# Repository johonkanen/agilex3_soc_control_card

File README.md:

# agilex3_soc_control_card
Agilex 5 SoC based control card for an AC in/out lab power supply.
The original board used an Agilex 3 FPGA and had a few bugs in the pin connections, so this second revision
uses an SoC instead of just an FPGA. The target is a Linux-capable control board with an Ethernet connection.

Main features:
- Agilex 5 E-Series SoC A5EB013B (quad-core HPS), B23B 795-ball package, -6S speed grade
- 1 GB LPDDR4 (SK hynix H9HCNNN8KUMLHR-NMO (fitted from stock; checked against the -NME data sheet), 2 channels x16 = x32), 2133 MT/s on the HPS EMIF
- 16 GB eMMC (KIOXIA THGAMVG7T13BAIL, 8-bit, HPS SD/MMC)
- 128 Mbit QSPI configuration flash (ISSI IS25WP128-RHLE)
- 1 Gb Ethernet (Realtek RTL8211FDI RGMII PHY, HanRun HR911130A MagJack)
- muxed ADC block (ADS7056)

Controls power electronics, so it mostly does generic I/O for PWM and SPI/SDM ADCs.
Built by JLCPCB (8-layer, JLC08161H-3313 stack-up).

The LPDDR4, eMMC and QSPI flash are parts shared with the Agilex 3 card and the Efinix Ti135 board, see
`SHARED_PARTS.md`.

## Status

- **LPDDR4 routing: done and tuned (2026-10-31).** All 54 nets (U7 bank 3 to U12) are routed and delay-matched
  with KiCad's time-domain tuner against the Altera 821801 budgets (`LPDDR4_DELAY_REPORT.md`, generated by
  `tools/lpddr4_delay/delay_report.py`):
  - byte spreads 4.5 / 8.8 / 4.5 / 3.3 ps (target 10 ps), DQ-DQS -4.5 ... +8.8 ps (limit -68 ... +43 ps);
  - DQS and CK P/N within 0.1 ps (limit 1 ps), CA/CKE/CS 415.0-417.7 ps die to ball (CK + 10 ps target);
  - no LPDDR4 DRC items, including the 0.2 / 0.3 mm crosstalk spacing rules.
  - IBIS simulation of the routed copper (`sim/lpddr4_si/results/routed.md`): every eye passes at 1600 MT/s
    (typ/min/max corners) and 2133 MT/s (typ).
  - Quartus (`LPDDR4_SWIZZLE_PLAN.md`): the routed pinout and swizzle fit, and a 2133 MT/s build (the -6S
    maximum) meets timing. 2133 MT/s is the design rate.
- **Board fully routed (2026-11-01).** eMMC, QSPI, Ethernet (RGMII, MDI pairs to the MagJack, PHY power and GND
  pours) and the HPS peripherals are routed, all zones are refilled, and the plane outlines are tidied.
  - DRC: 0 errors, 0 unconnected items, 0 schematic-parity issues. The only warning left is J3's intentional
    footprint mismatch (smaller pads and holes than the library); J3's two board-edge items are excluded.
  - ERC: 0 errors, 0 warnings.
  - Ethernet rules in `agilex_3_soc.kicad_dru`: 0.1 mm clearance at the U10 QFN pins, MDI P/N skew 1.27 mm,
    uncoupled length 7 mm (the HR911130A pinout forces the pairs apart at the jack).
  - QSPI series resistors placed at U7 and simulated (`sim/qspi_si`); eMMC needs no length matching at HS200/HS400.
- **Pre-order review in progress.** Before the JLCPCB order, independent review streams check the frozen design;
  rules, scope and reports are in `review/README.md`.
  - A1, Agilex 5 U7 connectivity (every ball, configuration, HPS pin mux, full-pin Quartus fit): running.
  - A2 (power tree, other ICs, connectors), B (footprints, BOM, assembly) and C (fabrication, layout, SI): to follow.
  - Sources for the review: `docs/REVIEW_SOURCES.md`. Datasheets for every part: `docs/DATASHEETS.md`, downloaded
    with `tools/datasheets/fetch_datasheets.py` (git-ignored, copyrighted).
  - Open BOM item: J3 (2x19 1.27 mm socket) has no part number yet.

## Copper layers

<!-- board-plots:start -->
<!-- Generated by kicad-board-plots; edits between these markers are overwritten. -->

3D renders and copper layers of `agilex_3_soc.kicad_pcb`, the layers in stack order without silkscreen. Plotted by [kicad-board-plots](https://github.com/johonkanen/kicad-board-plots) on each board change; the images live on the `renders` branch.

<table>
<tr>
<td align="center"><br><b>3D, top</b></td>
<td align="center"><br><b>3D, bottom (seen from below)</b></td>
</tr>
<tr>
<td align="center"><br><b>F.Cu: signal (top)</b></td>
<td align="center"><br><b>In1.Cu: GND plane</b></td>
</tr>
<tr>
<td align="center"><br><b>In2.Cu: signal, PHY3V3 pour</b></td>
<td align="center"><br><b>In3.Cu: 1V2, 1V8 planes</b></td>
</tr>
<tr>
<td align="center"><br><b>In4.Cu: GND plane</b></td>
<td align="center"><br><b>In5.Cu: signal</b></td>
</tr>
<tr>
<td align="center"><br><b>In6.Cu: 3V3, 1V8, VCORE, GND, 1V2 and 1 more planes</b></td>
<td align="center"><br><b>B.Cu: signal + plane, 1V1, 3V3, GND, 1V2, VCORE and 4 more pours (bottom, seen from the top)</b></td>
</tr>
</table>

<!-- board-plots:end -->

## Credits

The Agilex 5 schematic sheets in `a5e_kicad/` started from the DBM_A5E013 example KiCad project by
Rolf (Altera), attached to his KiCad symbol library merge request
[kicad-symbols !5361](https://gitlab.com/kicad/libraries/kicad-symbols/-/merge_requests/5361), and have
since been heavily modified. The U7 symbol and the `Altera_B23B` footprint come from his Agilex symbol and
footprint generators ([kicad-symbols !5565](https://gitlab.com/kicad/libraries/kicad-symbols/-/merge_requests/5565),
[kicad-library-tools !2200](https://gitlab.com/kicad/libraries/kicad-library-tools/-/merge_requests/2200)).

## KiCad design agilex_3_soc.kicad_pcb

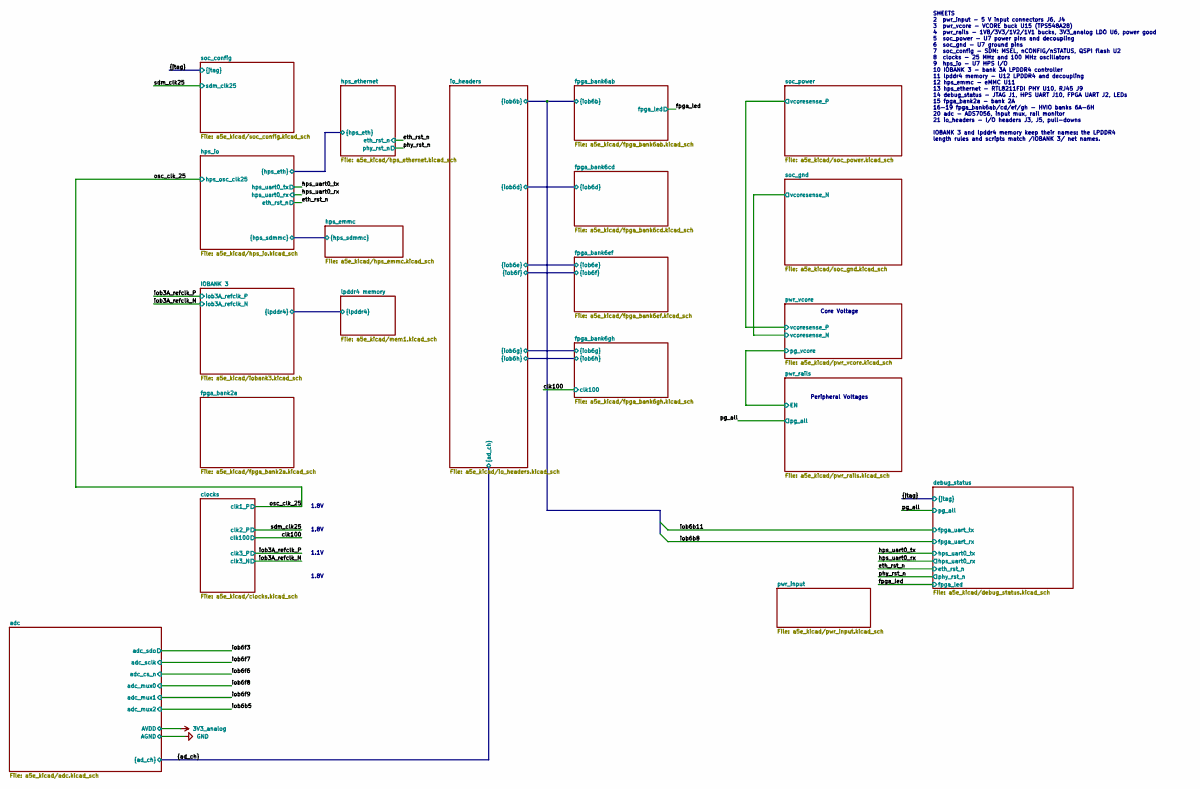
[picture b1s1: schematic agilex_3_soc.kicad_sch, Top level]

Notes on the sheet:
1.8V
Core Voltage
SHEETS 2 pwr_input - 5 V input connectors J6, J4 3 pwr_vcore - VCORE buck U15 (TPS548A28) 4 pwr_rails - 1V8/3V3/1V2/1V1 bucks, 3V3_analog LDO U6, power good 5 soc_power - U7 power pins and decoupling 6 soc_gnd - U7 ground pins 7 soc_config - SDM: MSEL, nCONFIG/nSTATUS, QSPI flash U2 8 clocks - 25 M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
Peripheral Voltages
1.1V

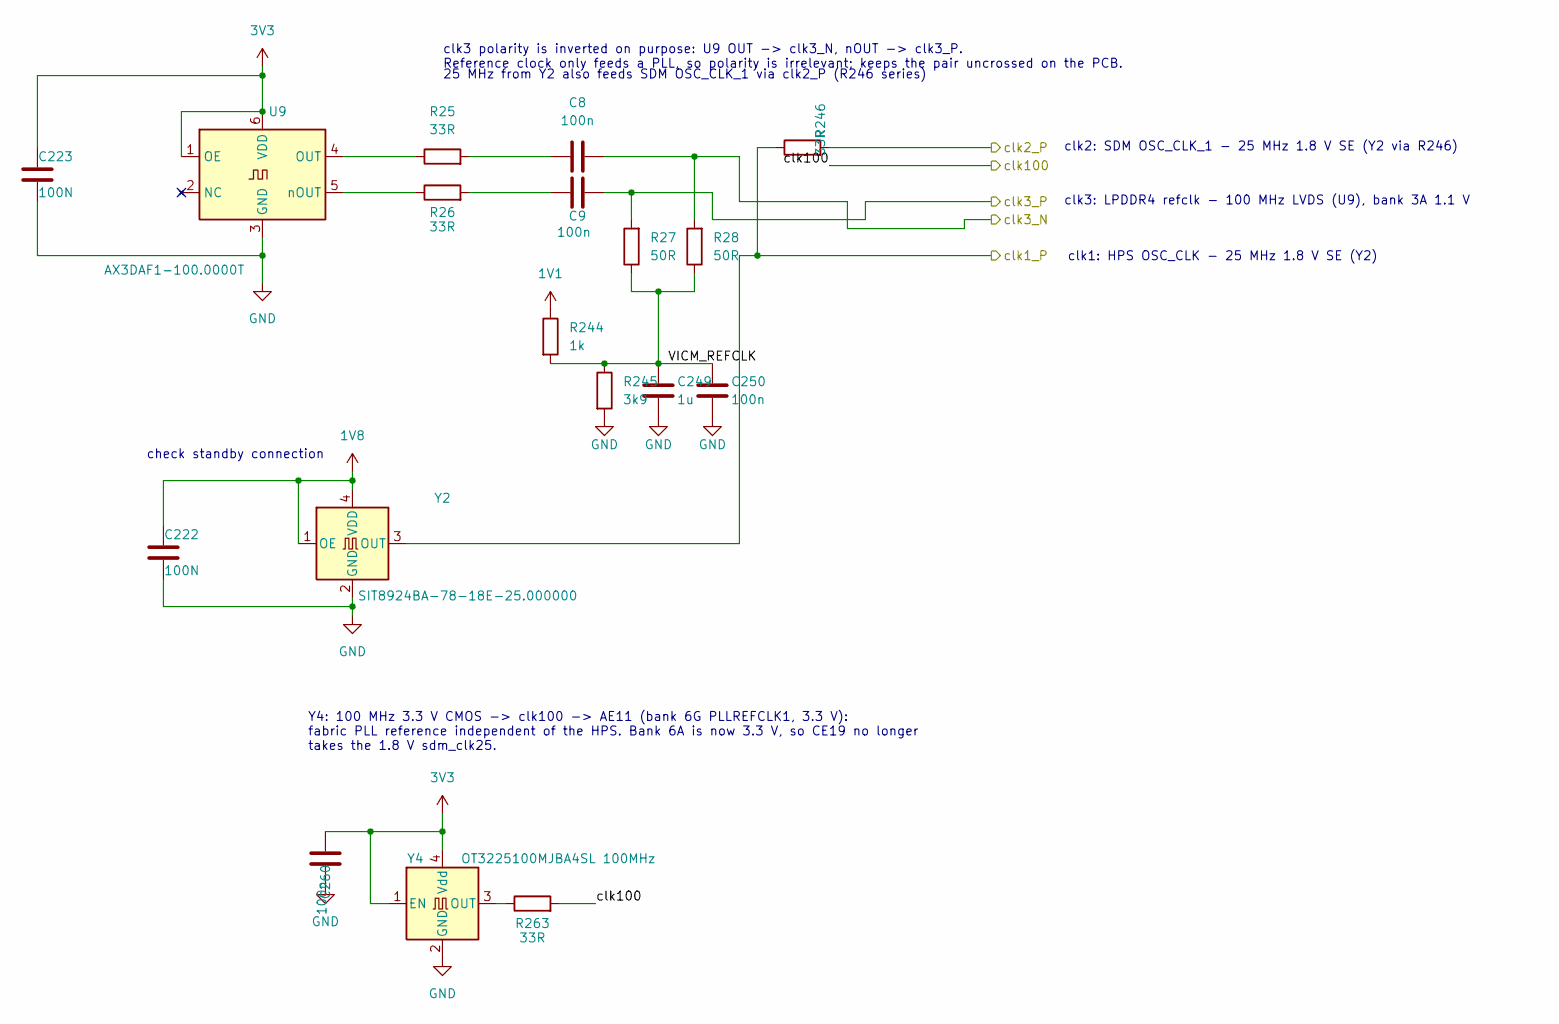
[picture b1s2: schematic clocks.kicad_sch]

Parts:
C8, C9, C250: 100n; C_0201_0603Metric; LCSC C190183
C222, C223: 100N; C_0201_0603Metric; LCSC C190183
C249: 1u; C_0201_0603Metric; LCSC C272877
C260: 100n; C_0402_1005Metric; LCSC C1525
R25, R26: 33R; R_0201_0603Metric; LCSC C320843
R27, R28: 50R; R_0402_1005Metric; LCSC C25120
R244: 1k; R_0201_0603Metric; LCSC C270365
R245: 3k9; R_0201_0603Metric; LCSC C473550
R246, R263: 33R; R_0402_1005Metric; LCSC C25105
U9: AX3DAF1-100.0000T; Oscillator_SMD_SiTime_SiT9121-6Pin_3.2x2.5mm; LCSC C2002827
Y2: SIT8924BA-78-18E-25.000000; Oscillator_SMD_SiT_PQFN-4Pin_2.0x1.6mm; LCSC C17247134
Y4: OT3225100MJBA4SL 100MHz; Oscillator_SMD_Abracon_ASE-4Pin_3.2x2.5mm; LCSC C4353707

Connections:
1V1: R244.1; also elsewhere on the board
1V8: C222.1, Y2.1 (OE), Y2.4 (VDD); also elsewhere on the board
3V3: C223.1, C260.1, U9.1 (OE), U9.6 (VDD), Y4.1 (EN), Y4.4 (Vdd); also elsewhere on the board
/clk100: R263.2; also elsewhere on the board
/clocks/VICM_REFCLK: C249.1, C250.1, R27.1, R28.1, R244.2, R245.1
/iob3A_refclk_N: C8.2, R28.2; also elsewhere on the board
/iob3A_refclk_P: C9.2, R27.2; also elsewhere on the board
/osc_clk_25: R246.1, Y2.3 (OUT); also elsewhere on the board
/sdm_clk25: R246.2; also elsewhere on the board
GND: C222.2, C223.2, C249.2, C250.2, C260.2, R245.2, U9.3 (GND), Y2.2 (GND), Y4.2 (GND); also elsewhere on the board
unnamed: C8.1, R25.2
unnamed: C9.1, R26.2
unnamed: R25.1, U9.4 (OUT)
unnamed: R26.1, U9.5 (nOUT)
unnamed: R263.1, Y4.3 (OUT)

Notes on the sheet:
25 MHz from Y2 also feeds SDM OSC_CLK_1 via clk2_P (R246 series)
Y4: 100 MHz 3.3 V CMOS -> clk100 -> AE11 (bank 6G PLLREFCLK1, 3.3 V): fabric PLL reference independent of the HPS. Bank 6A is now 3.3 V, so CE19 no longer takes the 1.8 V sdm_clk25.
clk3: LPDDR4 refclk - 100 MHz LVDS (U9), bank 3A 1.1 V
check standby connection
clk2: SDM OSC_CLK_1 - 25 MHz 1.8 V SE (Y2 via R246)
clk1: HPS OSC_CLK - 25 MHz 1.8 V SE (Y2)
clk3 polarity is inverted on purpose: U9 OUT -> clk3_N, nOUT -> clk3_P. Reference clock only feeds a PLL, so polarity is irrelevant; keeps the pair uncrossed on the PCB.

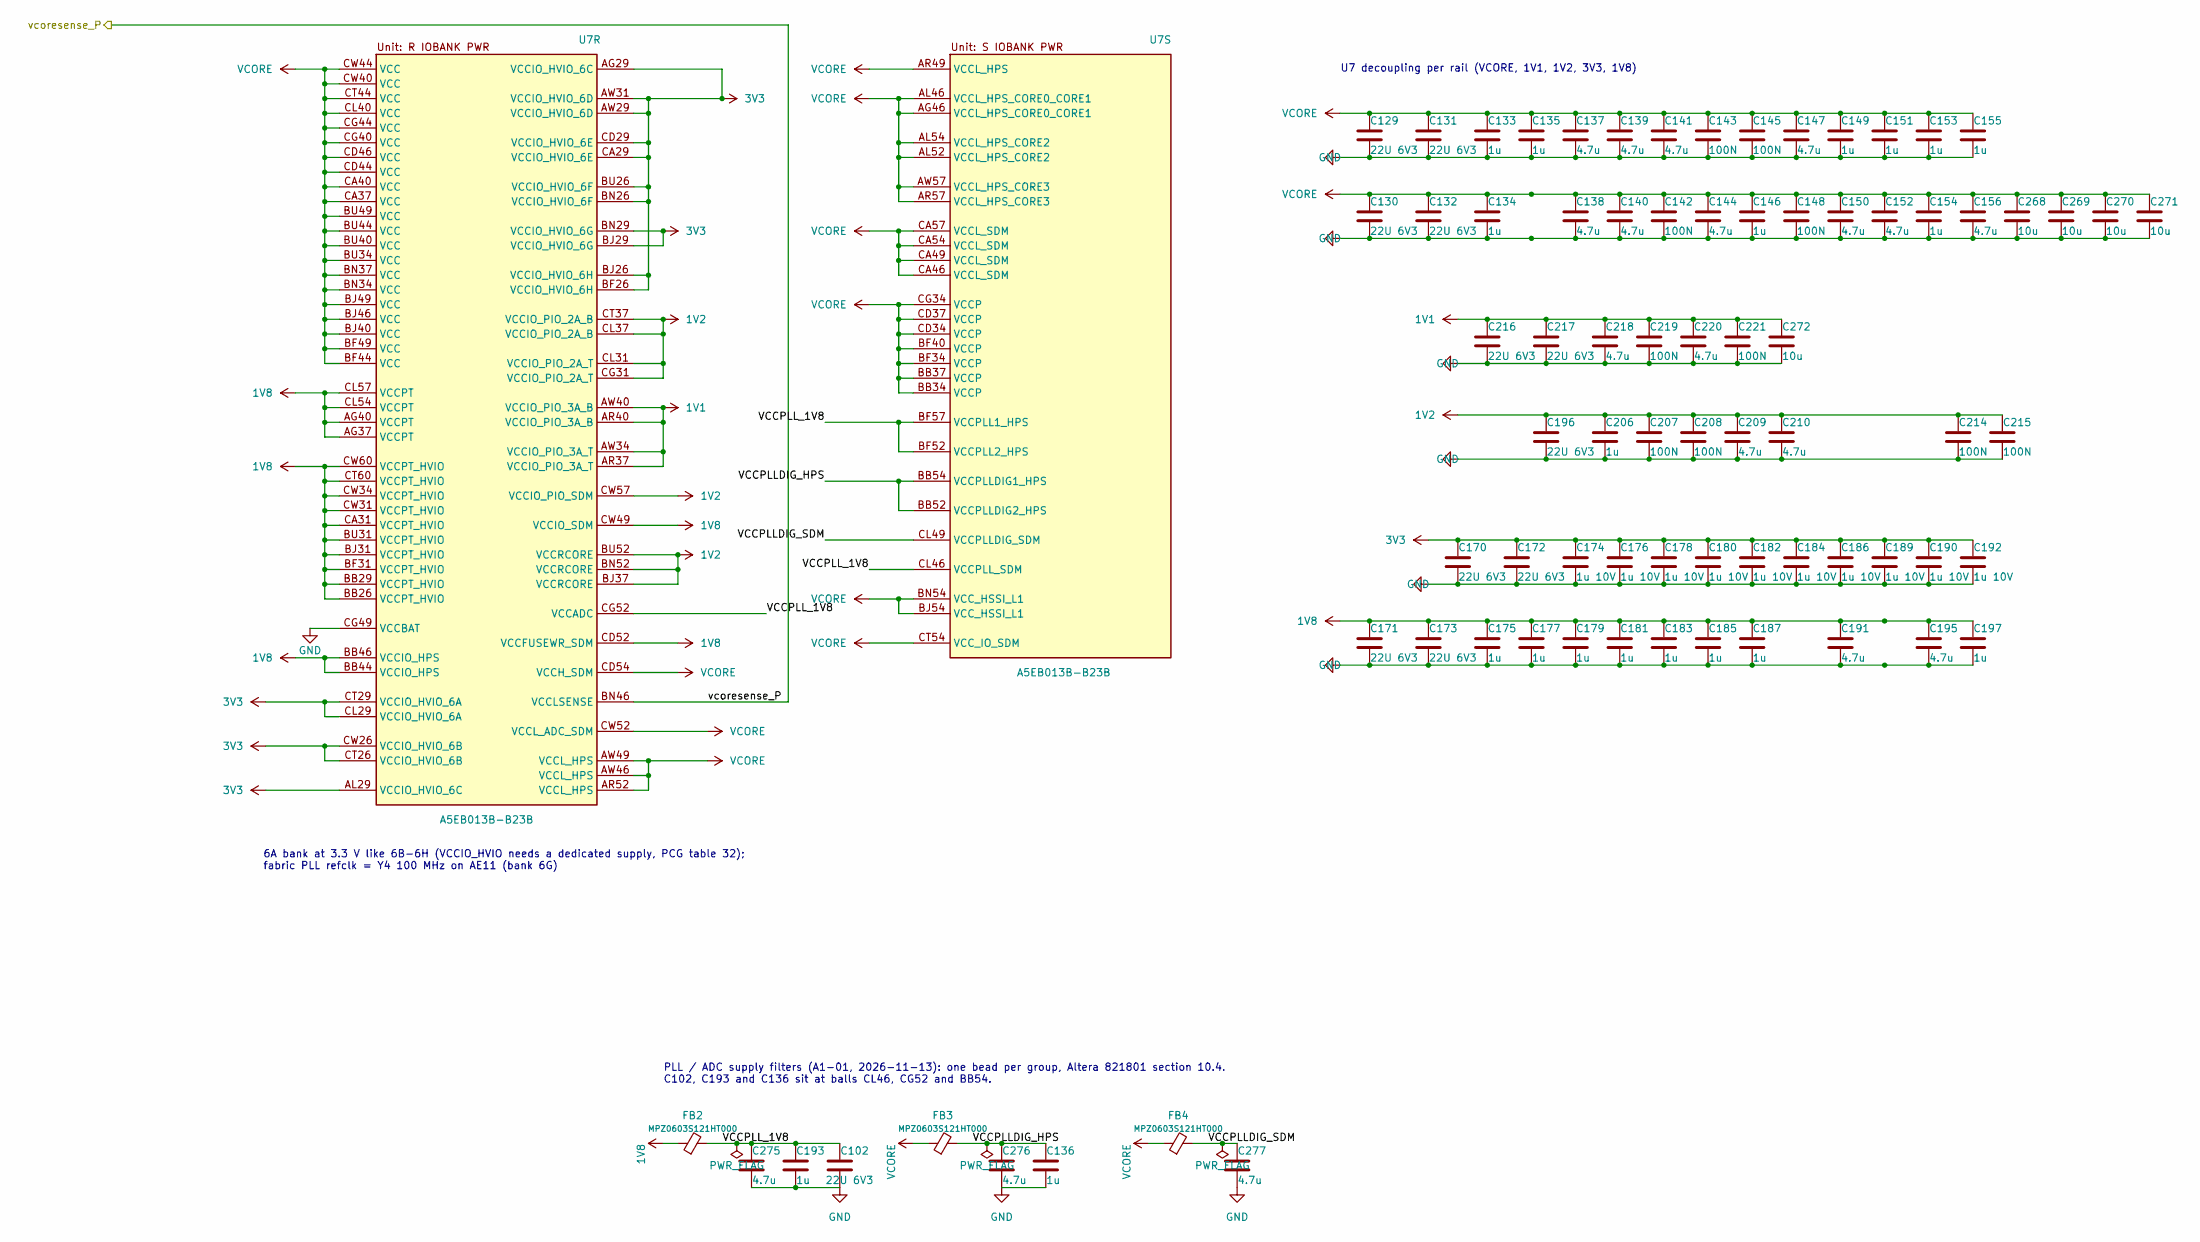
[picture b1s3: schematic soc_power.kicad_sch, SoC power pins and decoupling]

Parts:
C102, C129, C130, C131, C132, C170, C171, C172, C173, C196, C216, C217: 22U 6V3; C_0402_1005Metric; LCSC C415703
C133, C134, C135, C136, C146, C149, C151, C153, C154, C155, C175, C177, C179, C181, C183, C185, C187, C193, C197, C206: 1u; C_0201_0603Metric; LCSC C272877
C137, C138, C139, C140, C141, C144, C147, C150, C152, C156, C191, C195, C209, C210, C218, C220, C275, C276, C277: 4.7u; C_0201_0603Metric; LCSC C5969171
C142, C143, C145, C148, C207, C208, C214, C215, C219, C221: 100N; C_0201_0603Metric; LCSC C190183
C174, C176, C178, C180, C182, C184, C186, C189, C190, C192: 1u 10V; C_0201_0603Metric; LCSC C76935
C268, C269, C270, C271, C272: 10u; C_0402_1005Metric; LCSC C15525
FB2, FB3, FB4: MPZ0603S121HT000; L_0201_0603Metric; LCSC C695597
U7: A5EB013B-B23B; Altera_B23B

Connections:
1V1: C216.1, C217.1, C218.1, C219.1, C220.1, C221.1, C272.1, U7.AR37 (VCCIO_PIO_3A_T), U7.AR40 (VCCIO_PIO_3A_B), U7.AW34 (VCCIO_PIO_3A_T), U7.AW40 (VCCIO_PIO_3A_B); also elsewhere on the board
1V2: C196.1, C206.1, C207.1, C208.1, C209.1, C210.1, C214.1, C215.1, U7.BJ37 (VCCRCORE), U7.BN52 (VCCRCORE), U7.BU52 (VCCRCORE), U7.CG31 (VCCIO_PIO_2A_T), U7.CL31 (VCCIO_PIO_2A_T), U7.CL37 (VCCIO_PIO_2A_B), U7.CT37 (VCCIO_PIO_2A_B), U7.CW57 (VCCIO_PIO_SDM); also elsewhere on the board
1V8: C171.1, C173.1, C175.1, C177.1, C179.1, C181.1, C183.1, C185.1, C187.1, C191.1, C195.1, C197.1, FB2.1, U7.AG37 (VCCPT), U7.AG40 (VCCPT), U7.BB26 (VCCPT_HVIO), U7.BB29 (VCCPT_HVIO), U7.BB44 (VCCIO_HPS), U7.BB46 (VCCIO_HPS), U7.BF31 (VCCPT_HVIO), U7.BJ31 (VCCPT_HVIO), U7.BU31 (VCCPT_HVIO), U7.CA31 (VCCPT_HVIO), U7.CD52 (VCCFUSEWR_SDM), U7.CL54 (VCCPT), U7.CL57 (VCCPT), U7.CT60 (VCCPT_HVIO), U7.CW31 (VCCPT_HVIO), U7.CW34 (VCCPT_HVIO), U7.CW49 (VCCIO_SDM), U7.CW60 (VCCPT_HVIO); also elsewhere on the board
3V3: C170.1, C172.1, C174.1, C176.1, C178.1, C180.1, C182.1, C184.1, C186.1, C189.1, C190.1, C192.1, U7.AG29 (VCCIO_HVIO_6C), U7.AL29 (VCCIO_HVIO_6C), U7.AW29 (VCCIO_HVIO_6D), U7.AW31 (VCCIO_HVIO_6D), U7.BF26 (VCCIO_HVIO_6H), U7.BJ26 (VCCIO_HVIO_6H), U7.BJ29 (VCCIO_HVIO_6G), U7.BN26 (VCCIO_HVIO_6F), U7.BN29 (VCCIO_HVIO_6G), U7.BU26 (VCCIO_HVIO_6F), U7.CA29 (VCCIO_HVIO_6E), U7.CD29 (VCCIO_HVIO_6E), U7.CL29 (VCCIO_HVIO_6A), U7.CT26 (VCCIO_HVIO_6B), U7.CT29 (VCCIO_HVIO_6A), U7.CW26 (VCCIO_HVIO_6B); also elsewhere on the board
/soc_power/VCCPLLDIG_HPS: C136.1, C276.1, FB3.2, U7.BB52 (VCCPLLDIG2_HPS), U7.BB54 (VCCPLLDIG1_HPS)
/soc_power/VCCPLLDIG_SDM: C277.1, FB4.2, U7.CL49 (VCCPLLDIG_SDM)
/soc_power/VCCPLL_1V8: C102.1, C193.1, C275.1, FB2.2, U7.BF52 (VCCPLL2_HPS), U7.BF57 (VCCPLL1_HPS), U7.CG52 (VCCADC), U7.CL46 (VCCPLL_SDM)
/soc_power/vcoresense_P: U7.BN46 (VCCLSENSE); also elsewhere on the board
GND: C102.2, C129.2, C130.2, C131.2, C132.2, C133.2, C134.2, C135.2, C136.2, C137.2, C138.2, C139.2, C140.2, C141.2, C142.2, C143.2, C144.2, C145.2, C146.2, C147.2, C148.2, C149.2, C150.2, C151.2, C152.2, C153.2, C154.2, C155.2, C156.2, C170.2, C171.2, C172.2, C173.2, C174.2, C175.2, C176.2, C177.2, C178.2, C179.2, C180.2, C181.2, C182.2, C183.2, C184.2, C185.2, C186.2, C187.2, C189.2, C190.2, C191.2, C192.2, C193.2, C195.2, C196.2, C197.2, C206.2, C207.2, C208.2, C209.2, C210.2, C214.2, C215.2, C216.2, C217.2, C218.2, C219.2, C220.2, C221.2, C268.2, C269.2, C270.2, C271.2, C272.2, C275.2, C276.2, C277.2, U7.CG49 (VCCBAT); also elsewhere on the board
VCORE: C129.1, C130.1, C131.1, C132.1, C133.1, C134.1, C135.1, C137.1, C138.1, C139.1, C140.1, C141.1, C142.1, C143.1, C144.1, C145.1, C146.1, C147.1, C148.1, C149.1, C150.1, C151.1, C152.1, C153.1, C154.1, C155.1, C156.1, C268.1, C269.1, C270.1, C271.1, FB3.1, FB4.1, U7.AG46 (VCCL_HPS_CORE0_CORE1), U7.AL46 (VCCL_HPS_CORE0_CORE1), U7.AL52 (VCCL_HPS_CORE2), U7.AL54 (VCCL_HPS_CORE2), U7.AR49 (VCCL_HPS), U7.AR52 (VCCL_HPS), U7.AR57 (VCCL_HPS_CORE3), U7.AW46 (VCCL_HPS), U7.AW49 (VCCL_HPS), U7.AW57 (VCCL_HPS_CORE3), U7.BB34 (VCCP), U7.BB37 (VCCP), U7.BF34 (VCCP), U7.BF40 (VCCP), U7.BF44 (VCC), U7.BF49 (VCC), U7.BJ40 (VCC), U7.BJ46 (VCC), U7.BJ49 (VCC), U7.BJ54 (VCC_HSSI_L1), U7.BN34 (VCC), U7.BN37 (VCC), U7.BN54 (VCC_HSSI_L1), U7.BU34 (VCC), U7.BU40 (VCC), U7.BU44 (VCC), U7.BU49 (VCC), U7.CA37 (VCC), U7.CA40 (VCC), U7.CA46 (VCCL_SDM), U7.CA49 (VCCL_SDM), U7.CA54 (VCCL_SDM), U7.CA57 (VCCL_SDM), U7.CD34 (VCCP), U7.CD37 (VCCP), U7.CD44 (VCC), U7.CD46 (VCC), U7.CD54 (VCCH_SDM), U7.CG34 (VCCP), U7.CG40 (VCC), U7.CG44 (VCC), U7.CL40 (VCC), U7.CT44 (VCC), U7.CT54 (VCC_IO_SDM), U7.CW40 (VCC), U7.CW44 (VCC), U7.CW52 (VCCL_ADC_SDM); also elsewhere on the board

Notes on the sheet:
6A bank at 3.3 V like 6B-6H (VCCIO_HVIO needs a dedicated supply, PCG table 32); fabric PLL refclk = Y4 100 MHz on AE11 (bank 6G)
U7 decoupling per rail (VCORE, 1V1, 1V2, 3V3, 1V8)
PLL / ADC supply filters (A1-01, 2026-11-13): one bead per group, Altera 821801 section 10.4. C102, C193 and C136 sit at balls CL46, CG52 and BB54.

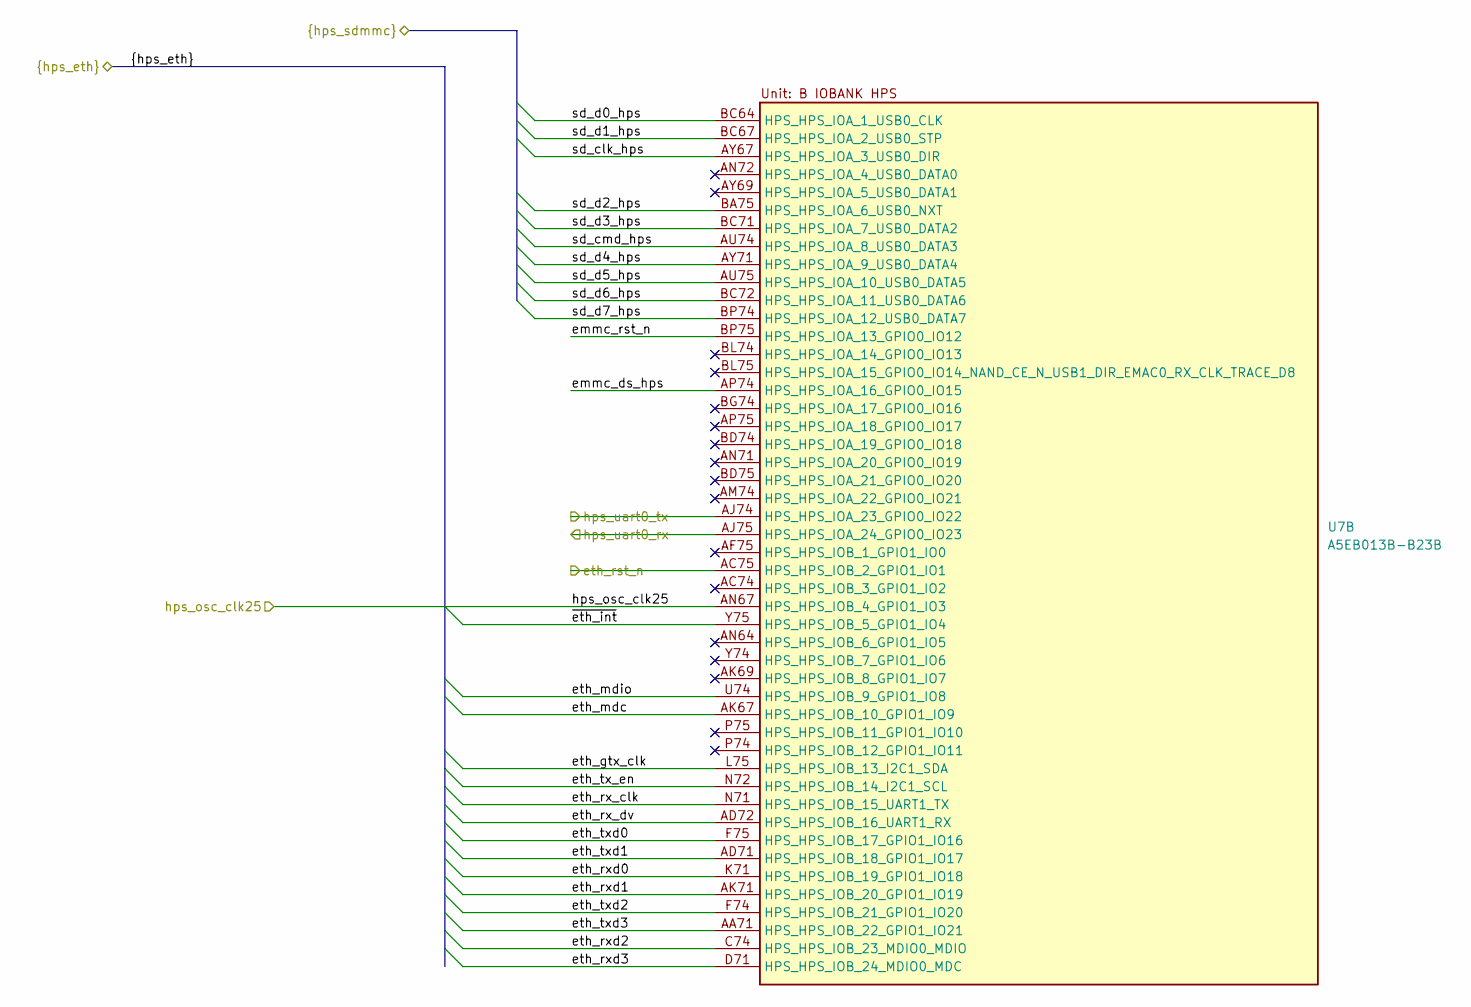
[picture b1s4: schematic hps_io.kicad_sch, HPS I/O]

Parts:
U7: A5EB013B-B23B; Altera_B23B

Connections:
/eth_rst_n: U7.AC75 (HPS_HPS_IOB_2_GPIO1_IO1); also elsewhere on the board
/hps_emmc/emmc_ds_hps: U7.AP74 (HPS_HPS_IOA_16_GPIO0_IO15); also elsewhere on the board
/hps_emmc/emmc_rst_n: U7.BP75 (HPS_HPS_IOA_13_GPIO0_IO12); also elsewhere on the board
/hps_emmc/sd_clk_hps: U7.AY67 (HPS_HPS_IOA_3_USB0_DIR); also elsewhere on the board
/hps_emmc/sd_cmd_hps: U7.AU74 (HPS_HPS_IOA_8_USB0_DATA3); also elsewhere on the board
/hps_emmc/sd_d0_hps: U7.BC64 (HPS_HPS_IOA_1_USB0_CLK); also elsewhere on the board
/hps_emmc/sd_d1_hps: U7.BC67 (HPS_HPS_IOA_2_USB0_STP); also elsewhere on the board
/hps_emmc/sd_d2_hps: U7.BA75 (HPS_HPS_IOA_6_USB0_NXT); also elsewhere on the board
/hps_emmc/sd_d3_hps: U7.BC71 (HPS_HPS_IOA_7_USB0_DATA2); also elsewhere on the board
/hps_emmc/sd_d4_hps: U7.AY71 (HPS_HPS_IOA_9_USB0_DATA4); also elsewhere on the board
/hps_emmc/sd_d5_hps: U7.AU75 (HPS_HPS_IOA_10_USB0_DATA5); also elsewhere on the board
/hps_emmc/sd_d6_hps: U7.BC72 (HPS_HPS_IOA_11_USB0_DATA6); also elsewhere on the board
/hps_emmc/sd_d7_hps: U7.BP74 (HPS_HPS_IOA_12_USB0_DATA7); also elsewhere on the board
/hps_io/eth_gtx_clk: U7.L75 (HPS_HPS_IOB_13_I2C1_SDA); also elsewhere on the board
/hps_io/eth_mdc: U7.AK67 (HPS_HPS_IOB_10_GPIO1_IO9); also elsewhere on the board
/hps_io/eth_mdio: U7.U74 (HPS_HPS_IOB_9_GPIO1_IO8); also elsewhere on the board
/hps_io/eth_rx_clk: U7.N71 (HPS_HPS_IOB_15_UART1_TX); also elsewhere on the board
/hps_io/eth_rx_dv: U7.AD72 (HPS_HPS_IOB_16_UART1_RX); also elsewhere on the board
/hps_io/eth_rxd0: U7.K71 (HPS_HPS_IOB_19_GPIO1_IO18); also elsewhere on the board
/hps_io/eth_rxd1: U7.AK71 (HPS_HPS_IOB_20_GPIO1_IO19); also elsewhere on the board
/hps_io/eth_rxd2: U7.C74 (HPS_HPS_IOB_23_MDIO0_MDIO); also elsewhere on the board
/hps_io/eth_rxd3: U7.D71 (HPS_HPS_IOB_24_MDIO0_MDC); also elsewhere on the board
/hps_io/eth_tx_en: U7.N72 (HPS_HPS_IOB_14_I2C1_SCL); also elsewhere on the board
/hps_io/eth_txd0: U7.F75 (HPS_HPS_IOB_17_GPIO1_IO16); also elsewhere on the board
/hps_io/eth_txd1: U7.AD71 (HPS_HPS_IOB_18_GPIO1_IO17); also elsewhere on the board
/hps_io/eth_txd2: U7.F74 (HPS_HPS_IOB_21_GPIO1_IO20); also elsewhere on the board
/hps_io/eth_txd3: U7.AA71 (HPS_HPS_IOB_22_GPIO1_IO21); also elsewhere on the board
/hps_io/~eth_int: U7.Y75 (HPS_HPS_IOB_5_GPIO1_IO4); also elsewhere on the board
/hps_uart0_rx: U7.AJ75 (HPS_HPS_IOA_24_GPIO0_IO23); also elsewhere on the board
/hps_uart0_tx: U7.AJ74 (HPS_HPS_IOA_23_GPIO0_IO22); also elsewhere on the board
/osc_clk_25: U7.AN67 (HPS_HPS_IOB_4_GPIO1_IO3); also elsewhere on the board

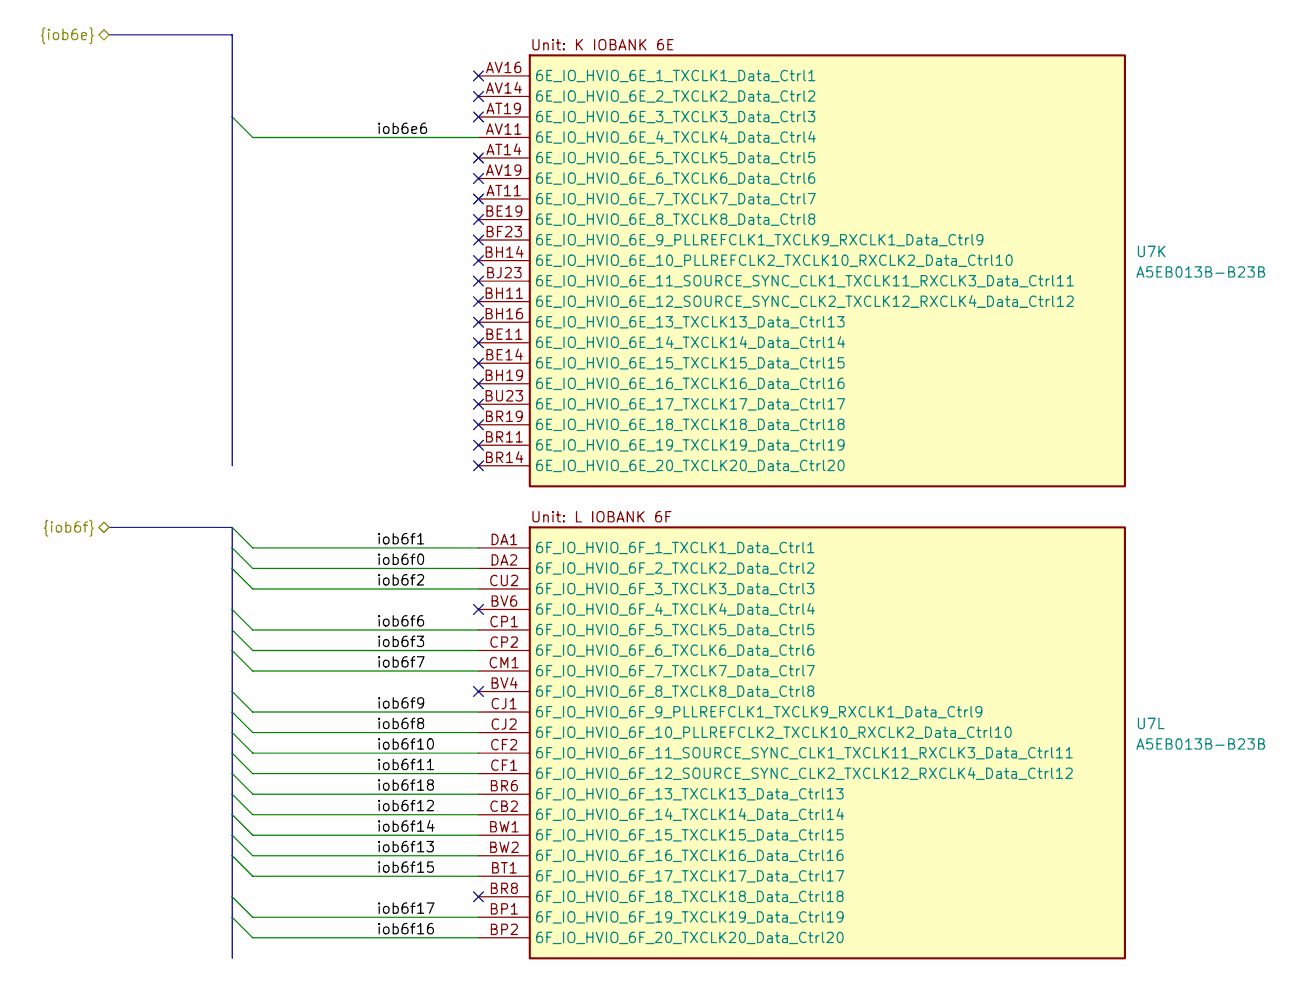
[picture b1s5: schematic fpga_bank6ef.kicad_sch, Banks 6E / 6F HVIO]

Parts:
U7: A5EB013B-B23B; Altera_B23B

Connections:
/fpga_bank6ef/iob6e6: U7.AV11 (6E_IO_HVIO_6E_4_TXCLK4_Data_Ctrl4); also elsewhere on the board
/fpga_bank6ef/iob6f0: U7.DA2 (6F_IO_HVIO_6F_2_TXCLK2_Data_Ctrl2); also elsewhere on the board
/fpga_bank6ef/iob6f1: U7.DA1 (6F_IO_HVIO_6F_1_TXCLK1_Data_Ctrl1); also elsewhere on the board
/fpga_bank6ef/iob6f2: U7.CU2 (6F_IO_HVIO_6F_3_TXCLK3_Data_Ctrl3); also elsewhere on the board
/fpga_bank6ef/iob6f3: U7.CP2 (6F_IO_HVIO_6F_6_TXCLK6_Data_Ctrl6); also elsewhere on the board
/fpga_bank6ef/iob6f6: U7.CP1 (6F_IO_HVIO_6F_5_TXCLK5_Data_Ctrl5); also elsewhere on the board
/fpga_bank6ef/iob6f7: U7.CM1 (6F_IO_HVIO_6F_7_TXCLK7_Data_Ctrl7); also elsewhere on the board
/fpga_bank6ef/iob6f8: U7.CJ2 (6F_IO_HVIO_6F_10_PLLREFCLK2_TXCLK10_RXC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); also elsewhere on the board
/fpga_bank6ef/iob6f9: U7.CJ1 (6F_IO_HVIO_6F_9_PLLREFCLK1_TXCLK9_RXCLK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); also elsewhere on the board
/fpga_bank6ef/iob6f10: U7.CF2 (6F_IO_HVIO_6F_11_SOURCE_SYNC_CLK1_TXCLK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); also elsewhere on the board
/fpga_bank6ef/iob6f11: U7.CF1 (6F_IO_HVIO_6F_12_SOURCE_SYNC_CLK2_TXCLK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); also elsewhere on the board
/fpga_bank6ef/iob6f12: U7.CB2 (6F_IO_HVIO_6F_14_TXCLK14_Data_Ctrl14); also elsewhere on the board
/fpga_bank6ef/iob6f13: U7.BW2 (6F_IO_HVIO_6F_16_TXCLK16_Data_Ctrl16); also elsewhere on the board
/fpga_bank6ef/iob6f14: U7.BW1 (6F_IO_HVIO_6F_15_TXCLK15_Data_Ctrl15); also elsewhere on the board
/fpga_bank6ef/iob6f15: U7.BT1 (6F_IO_HVIO_6F_17_TXCLK17_Data_Ctrl17); also elsewhere on the board
/fpga_bank6ef/iob6f16: U7.BP2 (6F_IO_HVIO_6F_20_TXCLK20_Data_Ctrl20); also elsewhere on the board
/fpga_bank6ef/iob6f17: U7.BP1 (6F_IO_HVIO_6F_19_TXCLK19_Data_Ctrl19); also elsewhere on the board
/fpga_bank6ef/iob6f18: U7.BR6 (6F_IO_HVIO_6F_13_TXCLK13_Data_Ctrl13); also elsewhere on the board

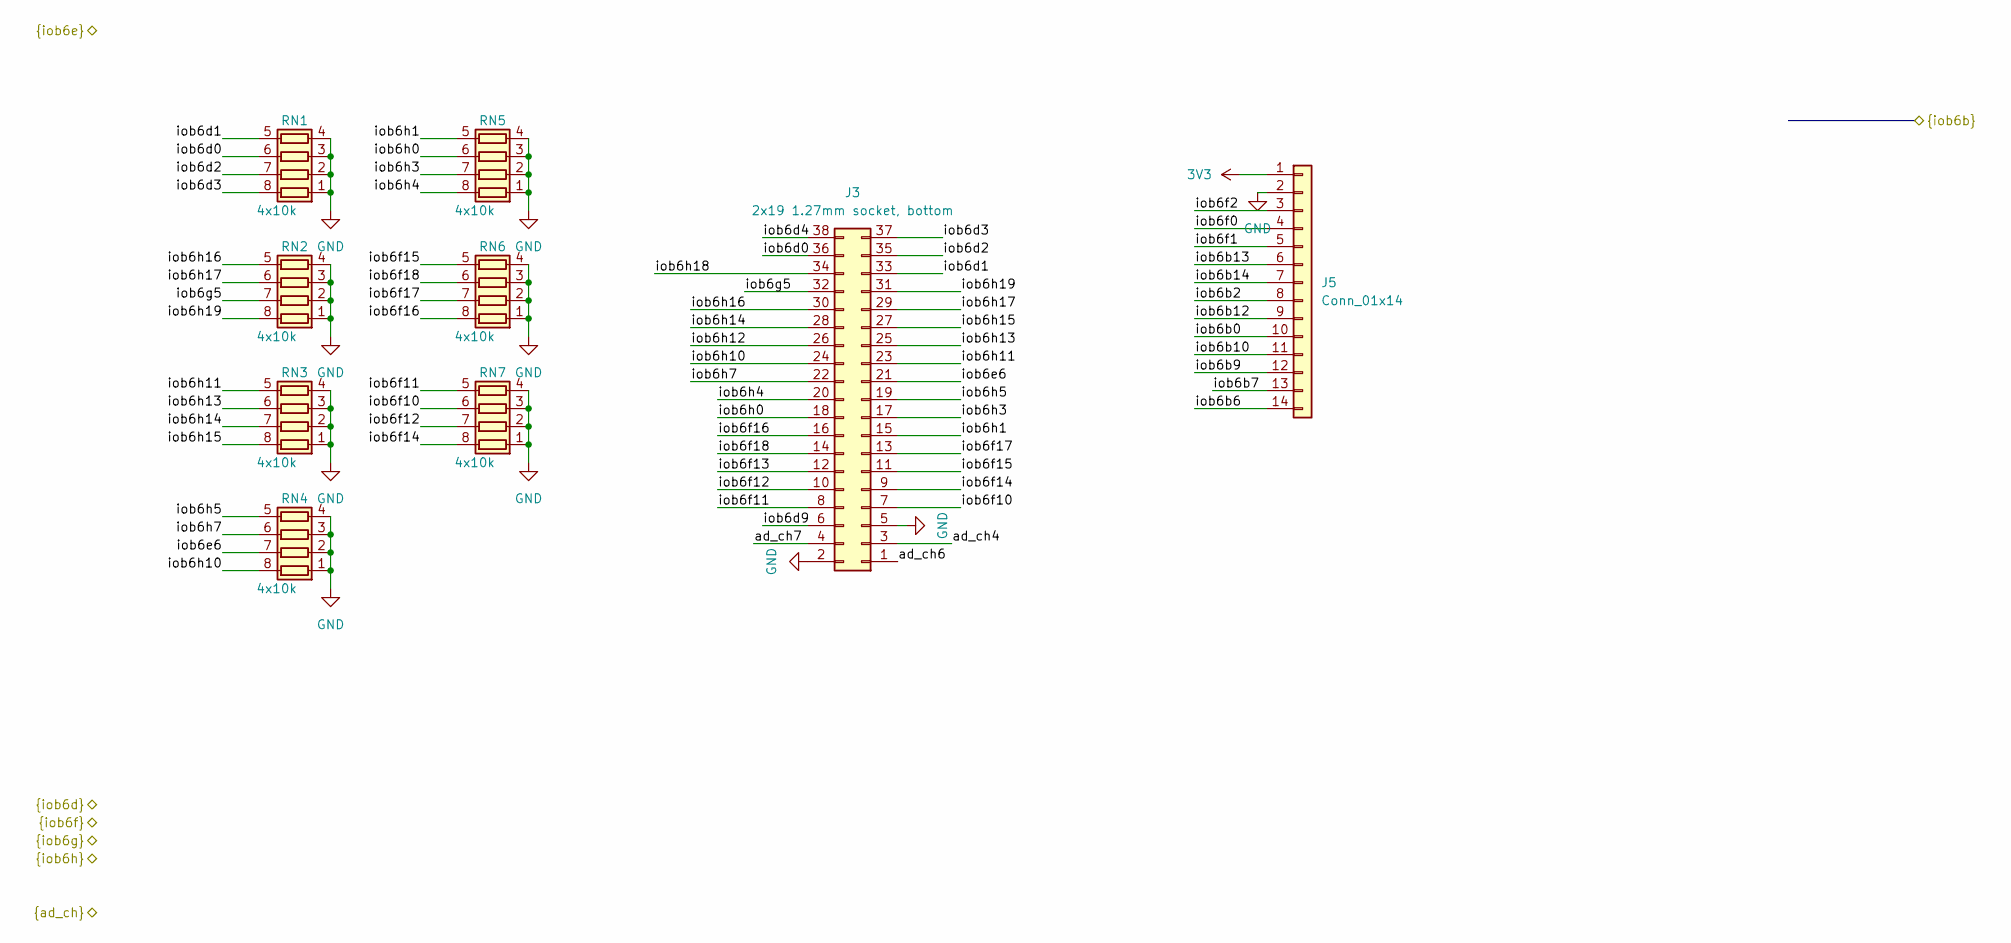
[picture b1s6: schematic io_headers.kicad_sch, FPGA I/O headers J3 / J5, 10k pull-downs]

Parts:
J3: 2x19 1.27mm socket, bottom; PinSocket_2x19_P1.27mm_Vertical; MPN HC-PM127-4.3H-2x19PZ; LCSC C27985219
J5: Conn_01x14; PinHeader_1x14_P2.54mm_Vertical; LCSC C22465874
RN1, RN2, RN3, RN4, RN5, RN6, RN7: 4x10k; R_Array_Convex_4x0402; LCSC C25725

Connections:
3V3: J5.1; also elsewhere on the board
/ad_ch4: J3.3; also elsewhere on the board
/ad_ch6: J3.1; also elsewhere on the board
/ad_ch7: J3.4; also elsewhere on the board
/fpga_bank6ab/iob6b0: J5.10; also elsewhere on the board
/fpga_bank6ab/iob6b2: J5.8; also elsewhere on the board
/fpga_bank6ab/iob6b6: J5.14; also elsewhere on the board
/fpga_bank6ab/iob6b7: J5.13; also elsewhere on the board
/fpga_bank6ab/iob6b9: J5.12; also elsewhere on the board
/fpga_bank6ab/iob6b10: J5.11; also elsewhere on the board
/fpga_bank6ab/iob6b12: J5.9; also elsewhere on the board
/fpga_bank6ab/iob6b13: J5.6; also elsewhere on the board
/fpga_bank6ab/iob6b14: J5.7; also elsewhere on the board
/fpga_bank6cd/iob6d0: J3.36, RN1.6 (R3.2); also elsewhere on the board
/fpga_bank6cd/iob6d1: J3.33, RN1.5 (R4.2); also elsewhere on the board
/fpga_bank6cd/iob6d2: J3.35, RN1.7 (R2.2); also elsewhere on the board
/fpga_bank6cd/iob6d3: J3.37, RN1.8 (R1.2); also elsewhere on the board
/fpga_bank6cd/iob6d4: J3.38; also elsewhere on the board
/fpga_bank6cd/iob6d9: J3.6; also elsewhere on the board
/fpga_bank6ef/iob6e6: J3.21, RN4.7 (R2.2); also elsewhere on the board
/fpga_bank6ef/iob6f0: J5.4; also elsewhere on the board
/fpga_bank6ef/iob6f1: J5.5; also elsewhere on the board
/fpga_bank6ef/iob6f2: J5.3; also elsewhere on the board
/fpga_bank6ef/iob6f10: J3.7, RN7.6 (R3.2); also elsewhere on the board
/fpga_bank6ef/iob6f11: J3.8, RN7.5 (R4.2); also elsewhere on the board
/fpga_bank6ef/iob6f12: J3.10, RN7.7 (R2.2); also elsewhere on the board
/fpga_bank6ef/iob6f13: J3.12; also elsewhere on the board
/fpga_bank6ef/iob6f14: J3.9, RN7.8 (R1.2); also elsewhere on the board
/fpga_bank6ef/iob6f15: J3.11, RN6.5 (R4.2); also elsewhere on the board
/fpga_bank6ef/iob6f16: J3.16, RN6.8 (R1.2); also elsewhere on the board
/fpga_bank6ef/iob6f17: J3.13, RN6.7 (R2.2); also elsewhere on the board
/fpga_bank6ef/iob6f18: J3.14, RN6.6 (R3.2); also elsewhere on the board
/fpga_bank6gh/iob6g5: J3.32, RN2.7 (R2.2); also elsewhere on the board
/fpga_bank6gh/iob6h0: J3.18, RN5.6 (R3.2); also elsewhere on the board
/fpga_bank6gh/iob6h1: J3.15, RN5.5 (R4.2); also elsewhere on the board
/fpga_bank6gh/iob6h3: J3.17, RN5.7 (R2.2); also elsewhere on the board
/fpga_bank6gh/iob6h4: J3.20, RN5.8 (R1.2); also elsewhere on the board
/fpga_bank6gh/iob6h5: J3.19, RN4.5 (R4.2); also elsewhere on the board
/fpga_bank6gh/iob6h7: J3.22, RN4.6 (R3.2); also elsewhere on the board
/fpga_bank6gh/iob6h10: J3.24, RN4.8 (R1.2); also elsewhere on the board
/fpga_bank6gh/iob6h11: J3.23, RN3.5 (R4.2); also elsewhere on the board
/fpga_bank6gh/iob6h12: J3.26; also elsewhere on the board
/fpga_bank6gh/iob6h13: J3.25, RN3.6 (R3.2); also elsewhere on the board
/fpga_bank6gh/iob6h14: J3.28, RN3.7 (R2.2); also elsewhere on the board
/fpga_bank6gh/iob6h15: J3.27, RN3.8 (R1.2); also elsewhere on the board
/fpga_bank6gh/iob6h16: J3.30, RN2.5 (R4.2); also elsewhere on the board
/fpga_bank6gh/iob6h17: J3.29, RN2.6 (R3.2); also elsewhere on the board
/fpga_bank6gh/iob6h18: J3.34; also elsewhere on the board
/fpga_bank6gh/iob6h19: J3.31, RN2.8 (R1.2); also elsewhere on the board
GND: J3.2, J3.5, J5.2, RN1.1 (R1.1), RN1.2 (R2.1), RN1.3 (R3.1), RN1.4 (R4.1), RN2.1 (R1.1), RN2.2 (R2.1), RN2.3 (R3.1), RN2.4 (R4.1), RN3.1 (R1.1), RN3.2 (R2.1), RN3.3 (R3.1), RN3.4 (R4.1), RN4.1 (R1.1), RN4.2 (R2.1), RN4.3 (R3.1), RN4.4 (R4.1), RN5.1 (R1.1), RN5.2 (R2.1), RN5.3 (R3.1), RN5.4 (R4.1), RN6.1 (R1.1), RN6.2 (R2.1), RN6.3 (R3.1), RN6.4 (R4.1), RN7.1 (R1.1), RN7.2 (R2.1), RN7.3 (R3.1), RN7.4 (R4.1); also elsewhere on the board
